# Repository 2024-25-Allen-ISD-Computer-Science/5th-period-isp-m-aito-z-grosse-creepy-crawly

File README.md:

# [Rover GUI Repo](https://github.com/grsszne/limes_ui_hunch)
# [Rover Firmware Repo](https://github.com/grsszne/limes_firmware)

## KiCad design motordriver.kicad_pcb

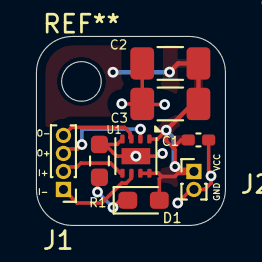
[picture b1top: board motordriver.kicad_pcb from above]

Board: 2 copper layers, 10.5 x 10.5 mm, 8 parts (0 on the bottom side), 7 nets.

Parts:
C1: 10000pF; C_0402_1005Metric_Pad0.74x0.62mm_HandSolder
C2: .1uF; C_1206_3216Metric_Pad1.33x1.80mm_HandSolder
C3: 22uF; C_1206_3216Metric_Pad1.33x1.80mm_HandSolder
D1: LED; LED_0603_1608Metric_Pad1.05x0.95mm_HandSolder
J1: Conn_01x04_Pin; PinHeader_1x04_P1.00mm_Vertical
J2: Conn_01x02_Pin; PinHeader_1x02_P1.00mm_Vertical
R1: 10K; R_0603_1608Metric_Pad0.98x0.95mm_HandSolder
U1: DRV8837; WSON-8-1EP_2x2mm_P0.5mm_EP0.9x1.6mm

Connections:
GND: C1.2, C2.2, C3.2, J2.2, R1.2, U1.4 (GND), U1.9 (GND)
IN+: J1.2, U1.5 (IN2)
IN-: J1.1, U1.6 (IN1)
unnamed: D1.1 (K), R1.1
OUT1: J1.3, U1.2 (OUT1)
OUT2: J1.4, U1.3 (OUT2)
VCC: C1.1, C2.1, C3.1, D1.2 (A), J2.1, U1.1 (VM), U1.7 (~SLEEP), U1.8 (VCC)

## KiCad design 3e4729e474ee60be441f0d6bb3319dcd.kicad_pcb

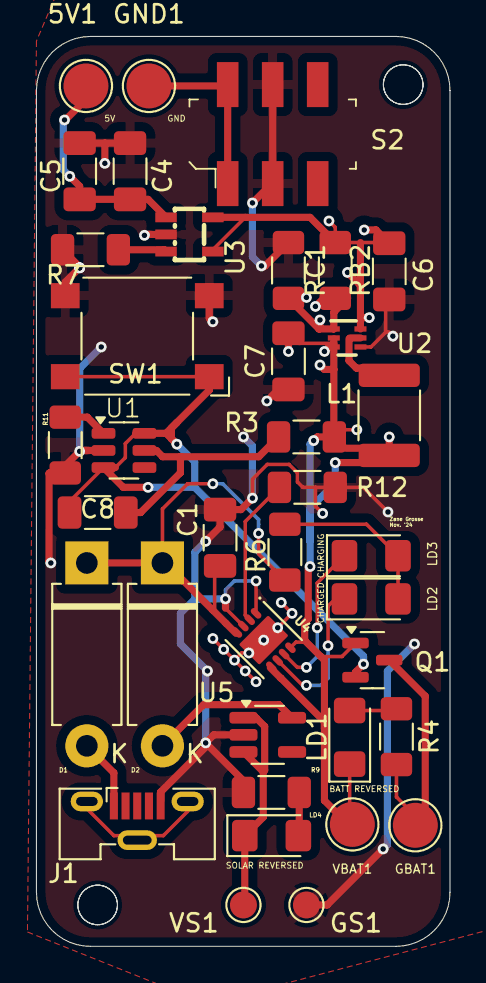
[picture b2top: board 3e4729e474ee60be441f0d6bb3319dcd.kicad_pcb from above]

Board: 2 copper layers, 23.0 x 50.5 mm, 37 parts (0 on the bottom side), 22 nets.

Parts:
5V1: TestPoint; TestPoint_Pad_D2.5mm
C1, C7: 22uF; C_1206_3216Metric_Pad1.33x1.80mm_HandSolder
C4: 100nF; C_1206_3216Metric_Pad1.33x1.80mm_HandSolder
C5: 10uF; C_1206_3216Metric_Pad1.33x1.80mm_HandSolder
C6: 47uF; C_1206_3216Metric_Pad1.33x1.80mm_HandSolder
C8: 0.1uF; C_1206_3216Metric_Pad1.33x1.80mm_HandSolder
D1, D2: 1N4007; D_DO-15_P10.16mm_Horizontal
GBAT1: TestPoint; TestPoint_Pad_D2.5mm
GND1: TestPoint; TestPoint_Pad_D2.5mm
GS1: TestPoint; TestPoint_Pad_D1.5mm
J1: USB_B_Micro; USB_Micro-B_Molex-105133-0031
L1: 1uH; L_1812_4532Metric_Pad1.30x3.40mm_HandSolder
LD1, LD4: YELLOW WD; LED_1206_3216Metric_Pad1.42x1.75mm_HandSolder
LD2: GREEN IND; LED_1206_3216Metric_Pad1.42x1.75mm_HandSolder
LD3: RED IND; LED_1206_3216Metric_Pad1.42x1.75mm_HandSolder
Q1: AO3400A; SOT-23
R3: 2K; R_1206_3216Metric_Pad1.30x1.75mm_HandSolder
R4, R9, R11: 1K; R_1206_3216Metric_Pad1.30x1.75mm_HandSolder
R6: 10K; R_1206_3216Metric_Pad1.30x1.75mm_HandSolder
R7: 6.2K; R_1206_3216Metric_Pad1.30x1.75mm_HandSolder
R12: 100R; R_1206_3216Metric_Pad1.30x1.75mm_HandSolder
RB2: 910K; R_1206_3216Metric_Pad1.30x1.75mm_HandSolder
RC1: 100K; R_1206_3216Metric_Pad1.30x1.75mm_HandSolder
S2: JS202011SCQN; Switch_Slide_JS202011SCQN
SW1: SW_Omron_B3FS; SW_SPST_Omron_B3FS-100xP
U1: DW06D
U2: TPS61023DRLR; DRL0006A
U3: SY6280; SOT23-5
U4: CN3065; DFN300X300X90-9N
U5: AP2127K-4.75; SOT-23-5_HandSoldering
VBAT1: TestPoint; TestPoint_Pad_D2.5mm
VS1: TestPoint; TestPoint_Pad_D1.5mm

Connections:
/3V7 -> 5V Boost: C6.2, RB2.1, U2.6 (VOUT), U3.4 (EN), U3.5 (IN)
GND: C1.2, C4.1, C5.1, C6.1, C7.1, GS1.1, J1.5 (GND), R3.2, R7.2, R9.2, R11.2, RC1.2, S2.2, S2.5, SW1.2, U1.2 (S1), U2.4 (GND), U3.2 (GND), U4.1 (TEMP), U4.3 (GND), U5.2 (GND)
unnamed: D1.2 (A), J1.1 (VBUS)
unnamed: C1.1, D1.1 (K), D2.1 (K), R6.1, U4.4 (VIN)
unnamed: D2.2 (A), U5.5 (VOUT)
unnamed: GND1.1, S2.1, S2.4
unnamed: LD1.2 (A), R4.1
unnamed: LD2.2 (A), LD3.2 (A), R6.2
unnamed: LD2.1 (K), U4.6 (~DONE)
unnamed: LD3.1 (K), U4.7 (~CHRG)
unnamed: LD4.2 (A), R9.1
unnamed: GBAT1.1, Q1.3 (D), R4.2
unnamed: C8.1, Q1.2 (S), SW1.1, U1.3 (S2), U1.6 (VSS)
unnamed: R11.1, U1.1 (V-)
unnamed: C8.2, R12.2, U1.5 (VDD)
unnamed: RB2.2, RC1.1, U2.1 (FB)
unnamed: L1.2, U2.5 (SW)
unnamed: R7.1, U3.3 (ISET)
unnamed: 5V1.1, C4.2, C5.2, U3.1 (OUT)
unnamed: R3.1, U4.2 (ISET)
VBAT: C7.2, L1.1, LD1.1 (K), Q1.1 (G), R12.1, U2.2 (EN), U2.3 (VIN), U4.5 (BAT), U4.8 (FB), VBAT1.1
VSOLAR: LD4.1 (K), U5.1 (VIN), U5.3 (EN), VS1.1

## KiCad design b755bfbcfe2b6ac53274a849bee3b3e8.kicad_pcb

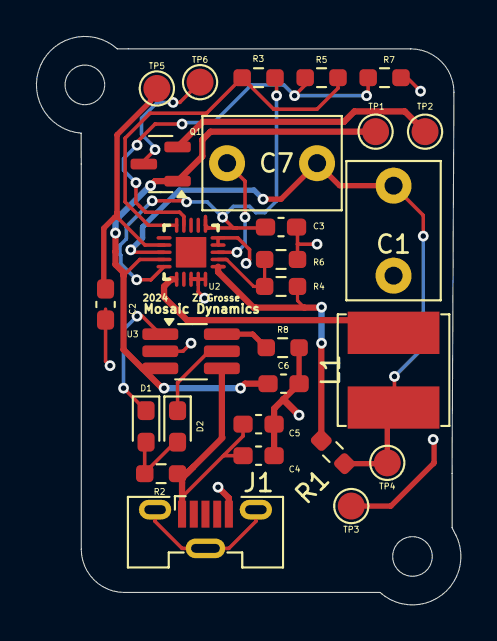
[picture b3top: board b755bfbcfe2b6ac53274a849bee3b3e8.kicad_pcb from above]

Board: 2 copper layers, 23.6 x 31.6 mm, 28 parts (0 on the bottom side), 17 nets.

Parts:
C1: 4.7uF; C_Disc_D7.5mm_W5.0mm_P5.00mm
C2: .1uF; C_0603_1608Metric_Pad1.08x0.95mm_HandSolder
C3: 100uF; C_0603_1608Metric_Pad1.08x0.95mm_HandSolder
C4, C6: 10uF; C_0603_1608Metric_Pad1.08x0.95mm_HandSolder
C5: 100nF; C_0603_1608Metric_Pad1.08x0.95mm_HandSolder
C7: 10nF; C_Disc_D7.5mm_W5.0mm_P5.00mm
D1, D2: LED; LED_0603_1608Metric_Pad1.05x0.95mm_HandSolder
J1: USB_B_Micro; USB_Micro-B_Molex-105133-0031
L1: L; L_Bourns_SRN6045TA
Q1: AO3400A; SOT-23
R1: 0R; R_0603_1608Metric_Pad0.98x0.95mm_HandSolder
R2, R8: R10K; R_0603_1608Metric_Pad0.98x0.95mm_HandSolder
R3: 6.2M; R_0603_1608Metric_Pad0.98x0.95mm_HandSolder
R4, R7: 3M; R_0603_1608Metric_Pad0.98x0.95mm_HandSolder
R5: 1M; R_0603_1608Metric_Pad0.98x0.95mm_HandSolder
R6: 9.1M; R_0603_1608Metric_Pad0.98x0.95mm_HandSolder
TP1: VBAT; TestPoint_Pad_D1.5mm
TP2: GBAT; TestPoint_Pad_D1.5mm
TP3: SG; TestPoint_Pad_D1.5mm
TP4: SIN; TestPoint_Pad_D1.5mm
TP5: 3V3; TestPoint_Pad_D1.5mm
TP6: GND; TestPoint_Pad_D1.5mm
U2: SPV1050TTR; QFN40P300X300X100-21N
U3: TP4057; TSOT-23-6_HandSoldering

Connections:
3V3: C2.2, TP5.1, U2.12 (LDO2)
GND: C1.1, C2.1, C3.1, C4.2, C5.1, C6.2, J1.5 (GND), Q1.3 (D), R6.1, R7.1, R8.2, TP3.1, TP6.1, U2.4 (GND), U2.5 (LDO1_EN), U2.18 (PGND), U2.19 (L_HV), U2.20 (IN_HV), U3.2 (GND)
unnamed: D1.2 (A), D2.2 (A), R2.2
unnamed: D1.1 (K), U3.1 (~CHRG)
unnamed: D2.1 (K), U3.5 (STDBY)
unnamed: C4.1, C5.2, J1.1 (VBUS), R2.1, U3.4 (V_{CC})
unnamed: Q1.2 (S), TP2.1
unnamed: R5.1, R7.2, U2.9 (EOC)
unnamed: L1.1, U2.16 (IN_LV)
unnamed: R1.1, R4.2, U2.1 (MPP)
unnamed: C7.2, U2.3 (MPP_REF)
unnamed: R4.1, R6.2, U2.2 (MPP_SET)
unnamed: R3.1, R5.2, U2.10 (UVP)
unnamed: R8.1, U3.6 (PROG)
SIN: C1.2, C7.1, L1.2, R1.2, TP4.1, U2.13 (CONF)
STORE: C3.2, R3.2, U2.6 (LDO2_EN), U2.15 (STORE)
VBAT: C6.1, Q1.1 (G), TP1.1, U2.14 (BATT), U3.3 (BAT)

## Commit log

2024-10-21 add online IDE url; add deadline
2024-11-22 Add files via upload
    Solar power manager PCB
2024-12-22 Create nothing_at_all
    To be deleted
2024-12-22 Delete nothing_at_all
    Deleted
2025-01-11 Create script.js
    Need to figure out angles and distance is not correct; not a JSON input, should automatically connect one point to next.
2025-01-11 Create data.json
    Sample.
2025-01-16 Points by distance reflected now
2025-01-16 Removed points, format is just distance
2025-01-16 Update README.md to reflect distance change
2025-01-16 Now actually accepts radian values + more comments
2025-01-31 Firmware Repo Added
